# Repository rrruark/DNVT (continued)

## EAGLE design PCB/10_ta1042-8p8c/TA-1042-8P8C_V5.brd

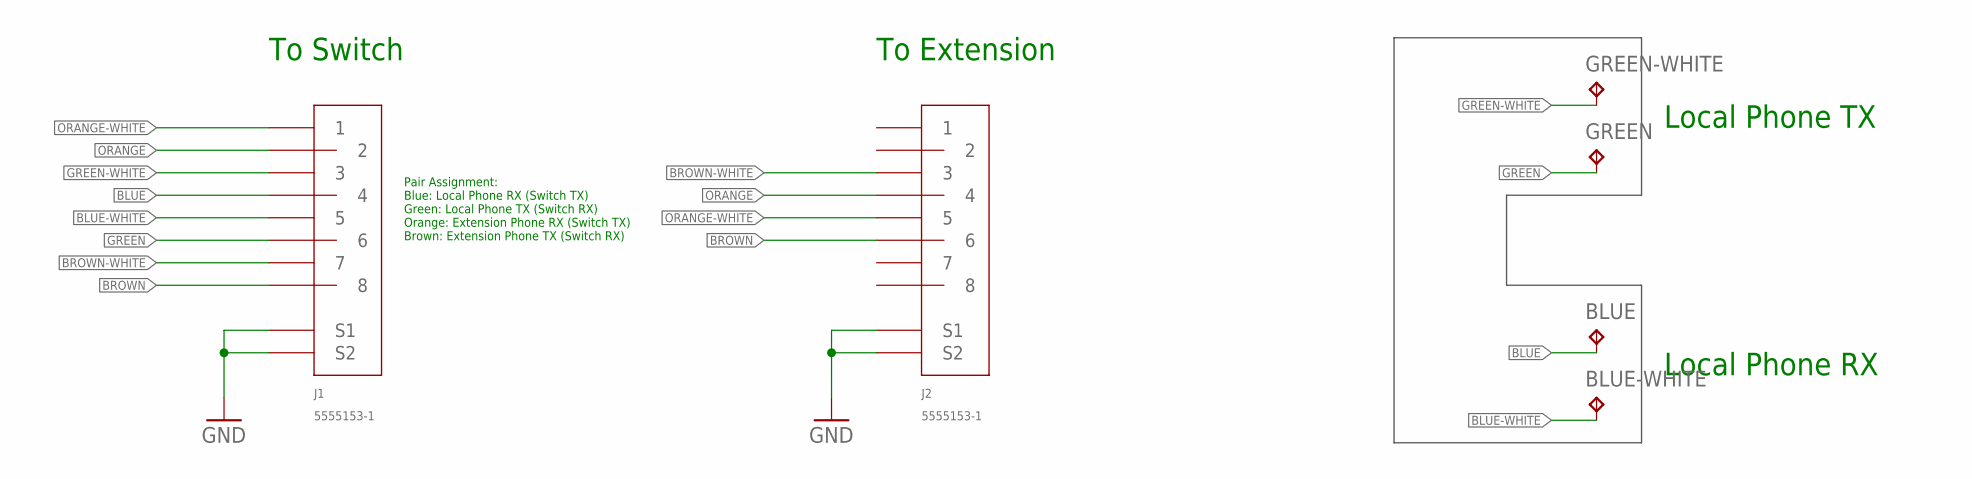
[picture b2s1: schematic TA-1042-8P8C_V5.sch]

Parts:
BLUE: TPTP20R; TP20R
BLUE-WHITE: TPTP20R; TP20R
GREEN: TPTP20R; TP20R
GREEN-WHITE: TPTP20R; TP20R
J1, J2: 5555153-1

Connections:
BLUE: BLUE.TP, J1.4
BLUE-WHITE: BLUE-WHITE.TP, J1.5
BROWN: J1.8, J2.6
BROWN-WHITE: J1.7, J2.3
GND: J1.S1, J1.S2, J2.S1, J2.S2
GREEN: GREEN.TP, J1.6
GREEN-WHITE: GREEN-WHITE.TP, J1.3
ORANGE: J1.2, J2.4
ORANGE-WHITE: J1.1, J2.5

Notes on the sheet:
Pair Assignment: Blue: Local Phone RX (Switch TX) Green: Local Phone TX (Switch RX) Orange: Extension Phone RX (Switch TX) Brown: Extension Phone TX (Switch RX)
To Switch
To Extension
Local Phone TX
Local Phone RX

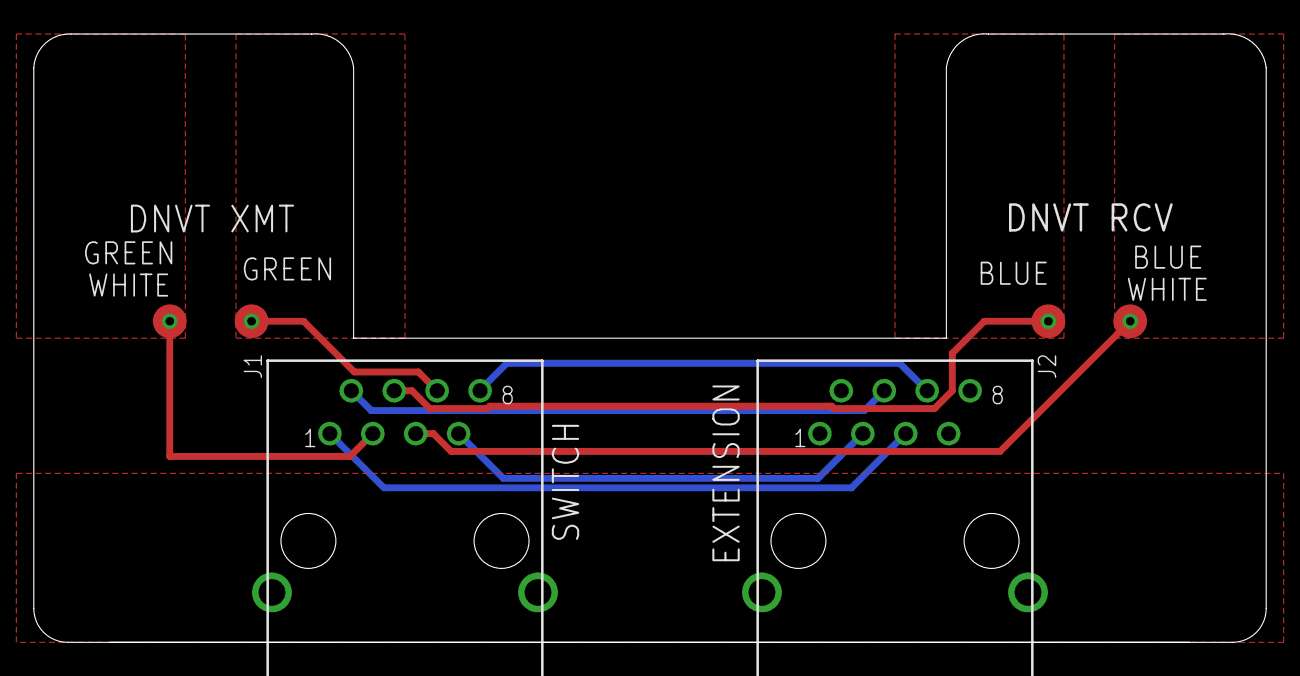
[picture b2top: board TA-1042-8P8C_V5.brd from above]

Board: 2 copper layers, 72.9 x 36.0 mm, 6 parts (0 on the bottom side), 9 nets.

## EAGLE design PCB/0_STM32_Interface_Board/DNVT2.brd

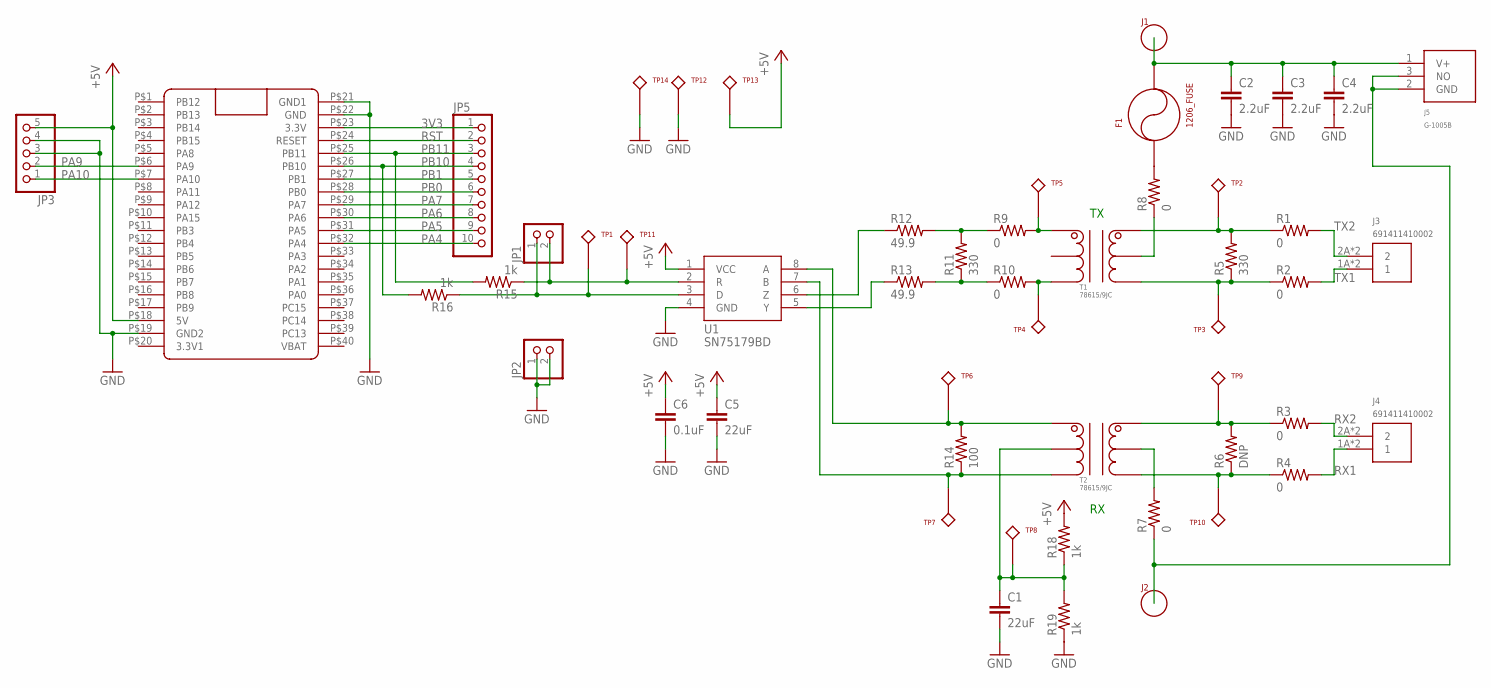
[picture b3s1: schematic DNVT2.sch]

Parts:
C1, C5: 22uF; 1210
C2, C3, C4: 2.2uF; 1210
C6: 0.1uF; 0603
F1: 1206_FUSE; 1206
J1, J2: BANANA
J3, J4: 691411410002
J5: G-1005B
JP1, JP2: PINHD-1X2; 1X02
JP3: PINHD-1X5; 1X05
JP5: PINHD-1X10; 1X10
R1, R2, R3, R4, R7, R8, R9, R10: 0; R0805
R5, R11: 330; R0805
R6: DNP; R0805
R12, R13: 49.9; R0805
R14: 100; R0805
R15, R16, R18, R19: 1k; 0603
T1, T2: 78615/9JC; 786
TP1, TP11, TP12, TP13, TP14: 5001
TP2, TP3, TP4, TP5, TP6, TP7, TP8, TP9, TP10: 5002; 5001
U1: SN75179BD; SOIC8
U$1: BLUE_PILL

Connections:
3V3: JP5.1, U$1.P$23 (3.3V)
+5V: C5.1, C6.1, JP3.5, R18.2, TP13.P$1, U1.1 (VCC), U$1.P$18 (5V)
GND: C1.2, C2.2, C3.2, C4.2, C5.2, C6.2, JP2.1, JP2.2, JP3.3, JP3.4, R19.1, TP12.P$1, TP14.P$1, U1.4 (GND), U$1.P$19 (GND2), U$1.P$21 (GND1), U$1.P$22 (GND)
unnamed: R1.1, R5.2, T1.6, TP2.P$1
unnamed: R2.1, R5.1, T1.4, TP3.P$1
unnamed: R3.1, R6.2, T2.6, TP9.P$1
unnamed: R4.1, R6.1, T2.4, TP10.P$1
unnamed: R7.2, T2.5
unnamed: R8.1, T1.5
unnamed: C1.1, R18.1, R19.2, T2.2, TP8.P$1
unnamed: R14.1, T2.3, TP7.P$1, U1.7 (B)
unnamed: R14.2, T2.1, TP6.P$1, U1.8 (A)
unnamed: R9.2, T1.1, TP5.P$1
unnamed: R10.2, T1.3, TP4.P$1
unnamed: R9.1, R11.2, R12.2
unnamed: R10.1, R11.1, R13.2
unnamed: R12.1, U1.6 (Z)
unnamed: R13.1, U1.5 (Y)
unnamed: F1.1, R8.2
unnamed: JP1.2, R15.1, TP11.P$1, U1.2 (R)
unnamed: C2.1, C3.1, C4.1, F1.2, J1.P$1, J5.1 (V+)
unnamed: JP1.1, R16.1, TP1.P$1, U1.3 (D)
PA4: JP5.10, U$1.P$32 (PA4)
PA5: JP5.9, U$1.P$31 (PA5)
PA6: JP5.8, U$1.P$30 (PA6)
PA7: JP5.7, U$1.P$29 (PA7)
PA9: JP3.2, U$1.P$6 (PA9)
PA10: JP3.1, U$1.P$7 (PA10)
PB0: JP5.6, U$1.P$28 (PB0)
PB1: JP5.5, U$1.P$27 (PB1)
PB10: JP5.4, R16.2, U$1.P$26 (PB10)
PB11: JP5.3, R15.2, U$1.P$25 (PB11)
RST: JP5.2, U$1.P$24 (RESET)
RTN: J2.P$1, J5.2 (GND), J5.3 (NO), R7.1
RX1: J4.1A (1), J4.1B (1), R4.2
RX2: J4.2A (2), J4.2B (2), R3.2
TX1: J3.1A (1), J3.1B (1), R2.2
TX2: J3.2A (2), J3.2B (2), R1.2

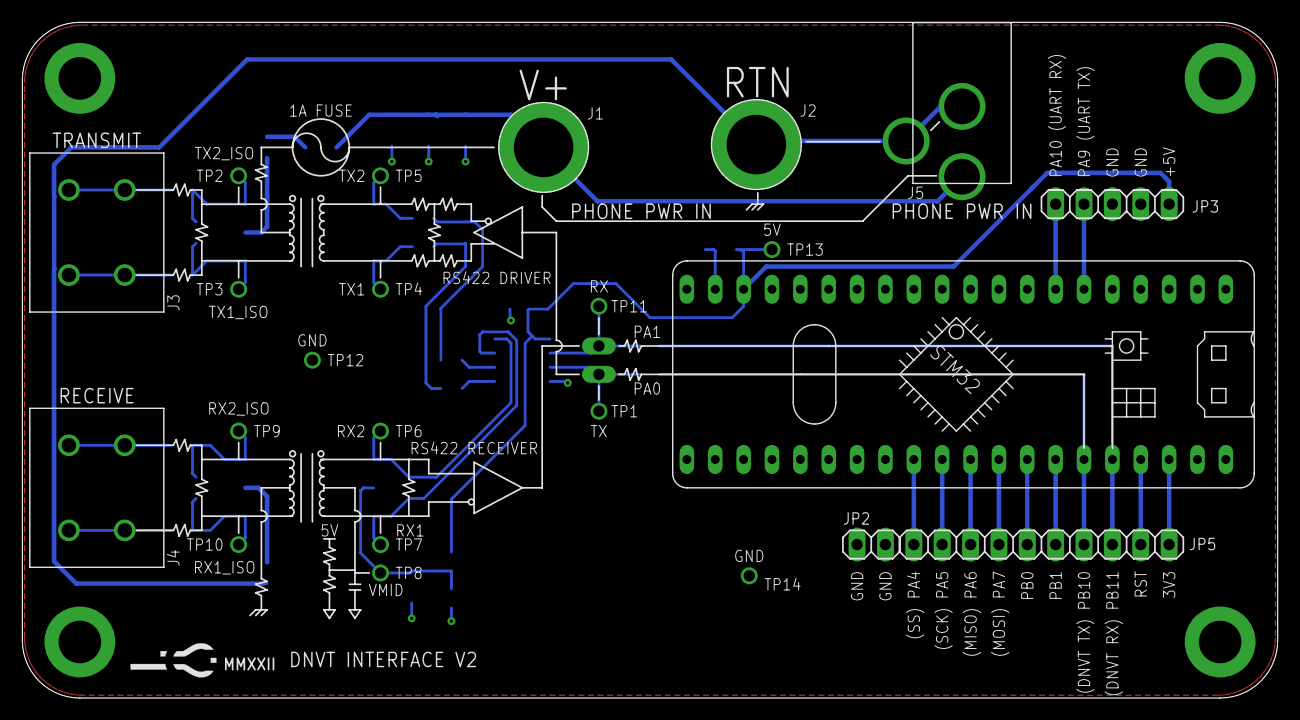
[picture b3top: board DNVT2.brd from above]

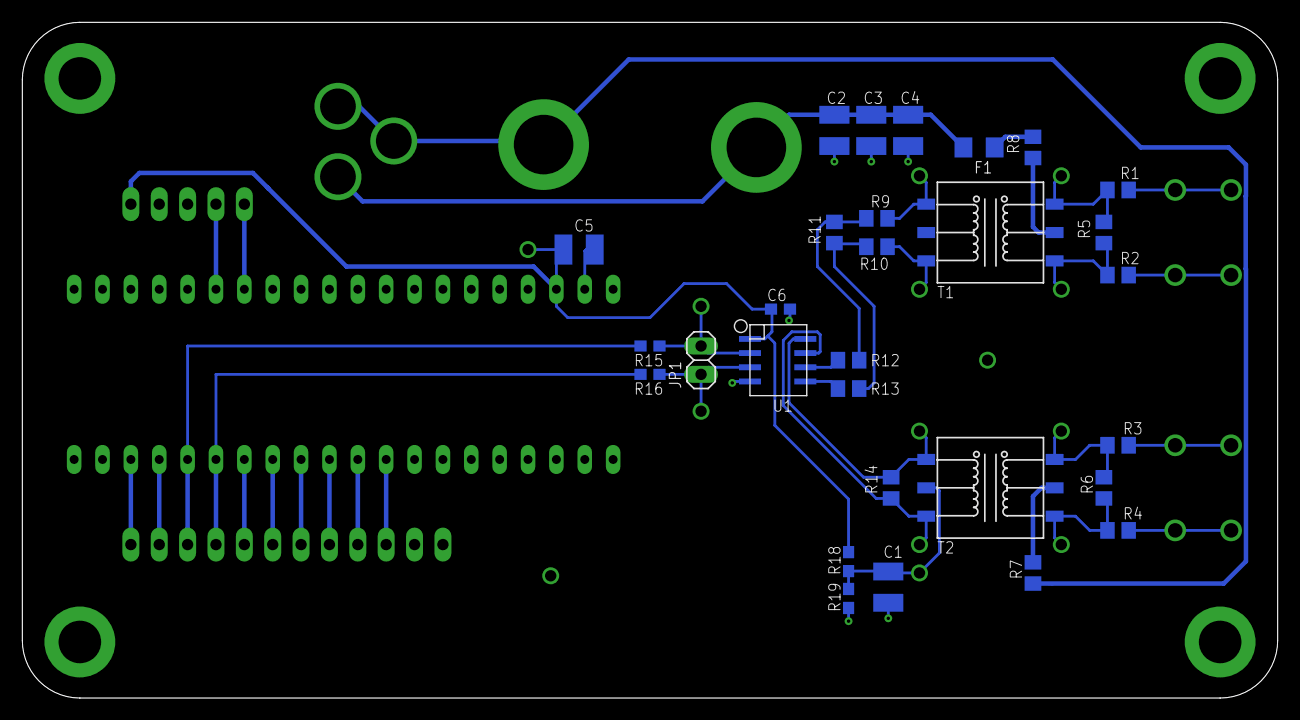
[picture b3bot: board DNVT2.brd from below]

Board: 2 copper layers, 112.4 x 60.5 mm, 52 parts (29 on the bottom side), 38 nets.

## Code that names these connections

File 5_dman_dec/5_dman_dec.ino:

/*
 * Crappy Differential Manchester Decoding.
 * This code chokes at 32kHz, but works for 16 kHz.
 * 
 * Robert Ruark
 * 2022
 */
#include <Arduino.h>

HardwareTimer timer(TIM1);
bool txVal = false;
bool process_next_bit   = true;
bool process_next_byte  = true;
bool current_bit        = 1;
byte current_byte       = 0x00;
int state               = 0;
byte tx_byte[5]         = {0xFF,0xEB,0x55,0x14,0xAA};
int bit_index           = 0;
int half_period_pos     = 0;
bool half_period_val[2] = {1,1};

int max_reps            = 10;
int reps                = 0;
int byte_position       = 0;
int short_count         = 0;

volatile bool reading   = 0;
volatile bool last_reading = 0;
volatile int reading_duration = 0;
volatile int last_reading_duration = 0;
volatile bool process_reading = false;

void OnTimer1Interrupt() 
{
    reading = digitalRead(PB11);
    //digitalWrite(PB10,reading);
    if(reading == last_reading)
    {
      reading_duration++;
    }
    else
    {
      last_reading_duration = reading_duration;
      reading_duration = 0;
      process_reading  = true;
    }
    last_reading = reading;
}

void setup() 
{
    //pinMode(PB10, OUTPUT);
    pinMode(PB0, OUTPUT);
    pinMode(PB11, INPUT);
    pinMode(PA7, INPUT_PULLUP);
    Serial.begin(1000000);
    // Configure timer
    timer.setPrescaleFactor(125); // Set prescaler to 2564 => timer frequency = 36MHz/125 = 288000 Hz
    timer.setOverflow(4); // Set overflow to 1 => timer frequency = 288000 Hz
    timer.attachInterrupt(OnTimer1Interrupt);
    timer.refresh(); // Make register changes take effect
    timer.resume(); // Start
}
void loop() 
{
  //Serial.println(last_reading_duration);
  if(process_reading)
  {
    process_reading = false;
    if(last_reading_duration>6)
    {
      current_byte = current_byte << 1;
      current_byte = current_byte | 1;
      short_count  = 0;
      bit_index++;
    }
    else
    {
      short_count++;
      if(short_count == 2)
      {
        current_byte = current_byte << 1;
        //current_byte = 0x00;
        bit_index++;
        short_count = 0;
      }
    }
    if(!short_count)
    {
      if(bit_index ==8)
      {
        Serial.print(current_byte,HEX);
        current_byte = 0x00;
        bit_index = 0;
      }
    }
  }
}

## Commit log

2023-01-14 Adding Python DMAN decoder and CPCW calculator
2023-01-21 Adding Interface Board PCB Design Files
2023-03-11 Adding switch PCB files
    V3 SMD
    V3 SMD RJ45
    V3 SMD Through hole transformers
    V3 SMD RJ45 Through hole transformers
2023-03-11 Adding back plates and boms
2023-03-16 Adding the rest of the BOMs
2023-03-16 Fixing readme for V3T
2023-03-19 Adding manual
2023-04-02 Added JLCPCB THT assembly files
    The new files for the V3RT design upload without errors and require no manual tweaks. JLCPCB will assemble all parts aside from the DC barrel jack and transformers which they do not have an acceptabl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
2023-04-02 Removing spurious lock file
2023-04-06 Corrected DC Barrel Jack Part Number
2023-04-11 Adding soldering fixture stl
2023-04-26 manual update
2023-04-26 Updated TA-1042 to RJ45 files
2023-05-02 V4 to eliminate emissions from OLED cable
